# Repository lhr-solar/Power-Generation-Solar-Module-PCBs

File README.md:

# Power-Generation-Solar-Module-PCBs

This repo will host the KiCAD module layout designs for the solar car, and
eventually subarray designs. Includes schematic symbols, footprints, and .step
models for solar cells and bypass diodes.

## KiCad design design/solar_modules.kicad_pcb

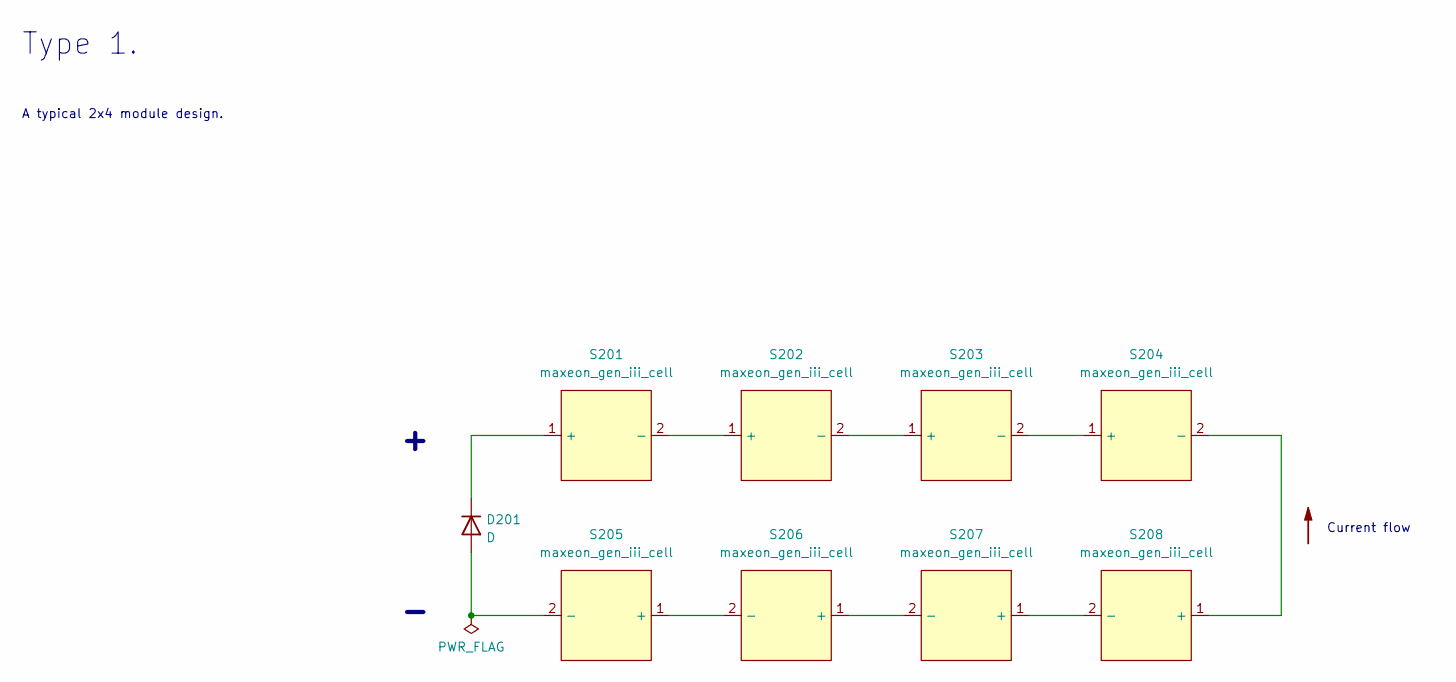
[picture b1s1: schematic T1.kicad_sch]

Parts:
D201: D; D_0201_0603Metric
S201, S202, S203, S204, S205, S206, S207, S208: maxeon_gen_iii_cell

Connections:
unnamed: D201.1 (K), S201.1 (+)
unnamed: D201.2 (A), S205.2 (-)
unnamed: S201.2 (-), S202.1 (+)
unnamed: S202.2 (-), S203.1 (+)
unnamed: S203.2 (-), S204.1 (+)
unnamed: S204.2 (-), S208.1 (+)
unnamed: S205.1 (+), S206.2 (-)
unnamed: S206.1 (+), S207.2 (-)
unnamed: S207.1 (+), S208.2 (-)

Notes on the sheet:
A typical 2x4 module design.
Current flow
Type 1.

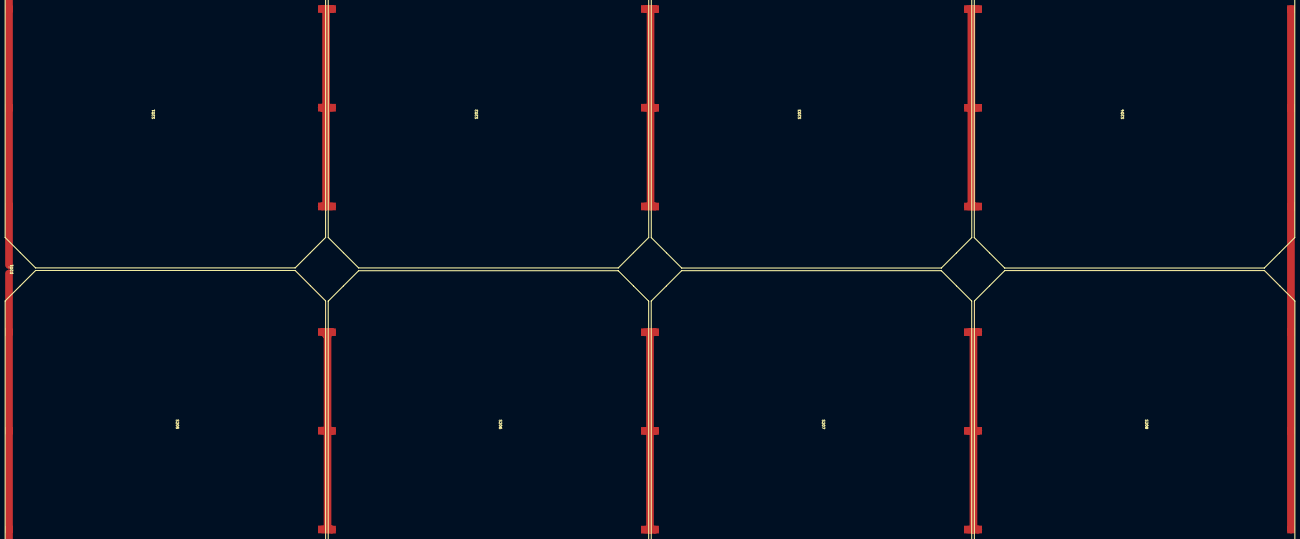
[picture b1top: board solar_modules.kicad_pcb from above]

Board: 2 copper layers, 9 parts (0 on the bottom side), 9 nets.

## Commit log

2022-08-03 init commit
